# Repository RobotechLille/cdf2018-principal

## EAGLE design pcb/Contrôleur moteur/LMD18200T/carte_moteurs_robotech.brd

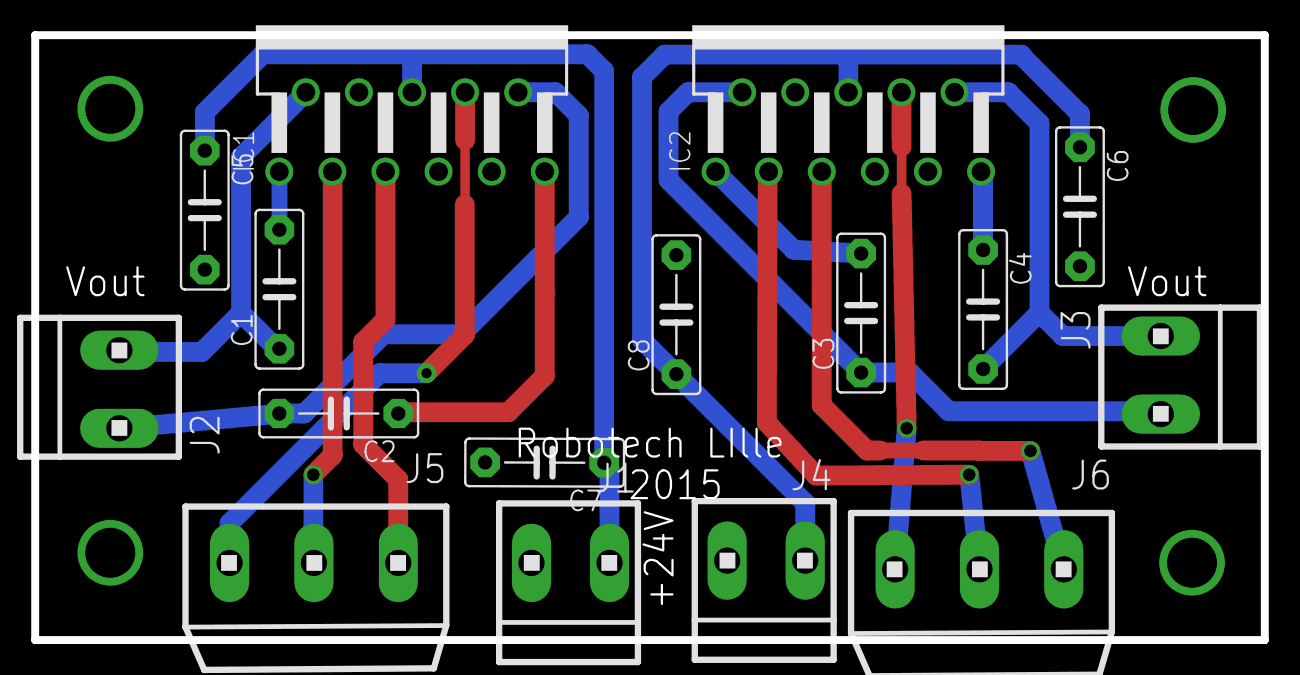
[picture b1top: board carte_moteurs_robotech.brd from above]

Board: 2 copper layers, 78.7 x 38.7 mm, 20 parts (0 on the bottom side), 16 nets.

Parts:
C1, C2, C3, C4: 10n; C7.5B3
C5, C6, C7, C8: 100n; C7.5B3
IC1, IC2: LM18200T; TO-220-11
J1, J2, J3, J4: MYJUMPER
J5, J6: 1X3MTA
U$1, U$2, U$3, U$4: DRILL3ME

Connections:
+24V: C5.1, C7.1, IC1.6, J1.2
DROITE_COURANT: IC2.8, J6.1
DROITE_PWM: IC2.5, J6.3
DROITE_S1: C3.1, IC2.2, J3.1
DROITE_S2: C4.2, IC2.10, J3.2
DROITE_SENS: IC2.3, J6.2
GAUCHE_COURANT: IC1.8, J5.1
GAUCHE_PWM: IC1.5, J5.3
GAUCHE_S1: C1.1, IC1.2, J2.1
GAUCHE_S2: C2.2, IC1.10, J2.2
GND: C5.2, C6.2, C7.2, C8.2, IC1.4, IC1.7, IC2.4, IC2.7, J1.1, J4.1, U$1.P$1, U$2.P$1, U$3.P$1, U$4.P$1
unnamed: C1.2, IC1.1
unnamed: C2.1, IC1.11
unnamed: C3.2, IC2.1
unnamed: C4.1, IC2.11
V_BAT2: C6.1, C8.1, IC2.6, J4.2

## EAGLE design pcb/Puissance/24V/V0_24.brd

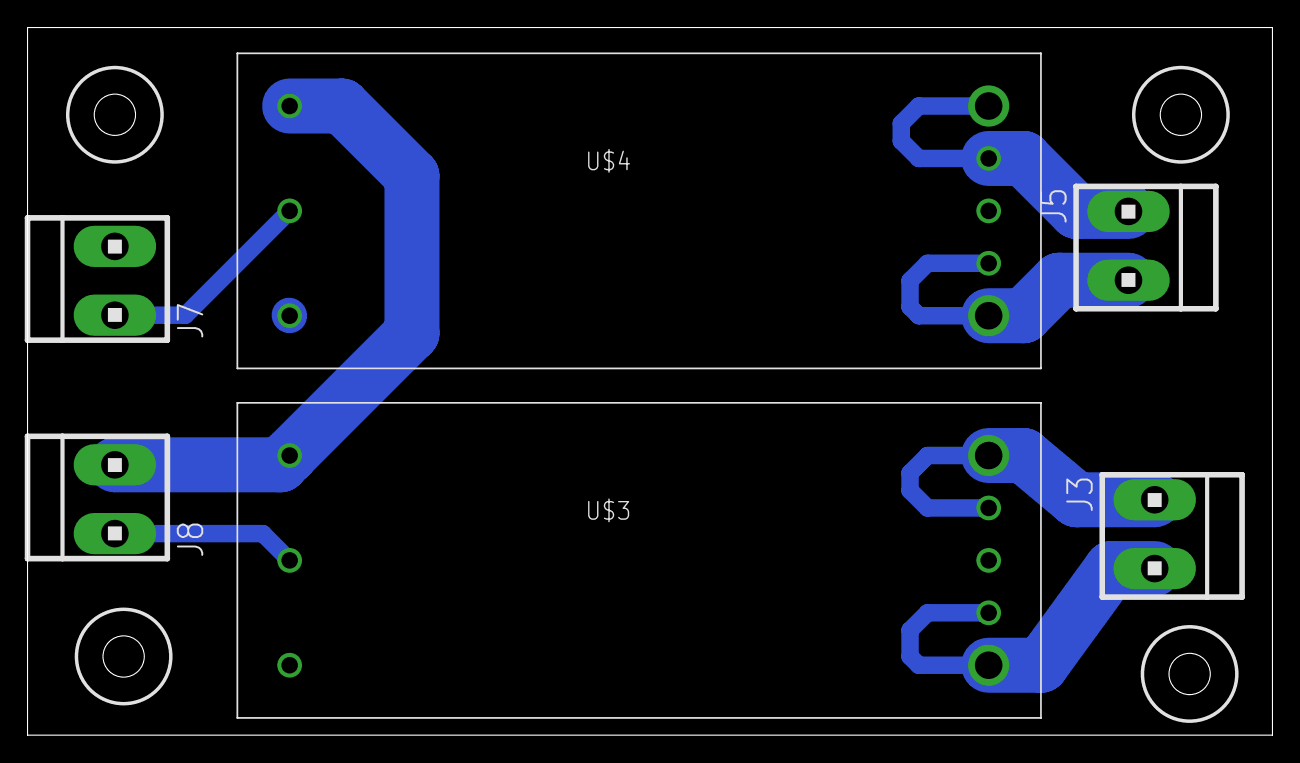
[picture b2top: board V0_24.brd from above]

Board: 2 copper layers, 90.5 x 51.4 mm, 10 parts (0 on the bottom side), 8 nets.

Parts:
J3, J5, J7, J8: MYJUMPER
U$1, U$2, U$5, U$6: DRIL-3
U$3, U$4: DC/DC_CONV_24V; UWE

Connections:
GND: J7.1, U$3.+VIN, U$4.+VIN
unnamed: J5.1, U$4.+SENSE, U$4.+VOUT
unnamed: J5.2, U$4.-SENSE, U$4.-VOUT
unnamed: J3.1, U$3.+SENSE, U$3.+VOUT
unnamed: J3.2, U$3.-SENSE, U$3.-VOUT
unnamed: J8.2, U$3.ON/OFF-CONTROL
S$2: J7.2, U$4.ON/OFF-CONTROL
S$3: J8.1, U$3.-VIN, U$4.-VIN

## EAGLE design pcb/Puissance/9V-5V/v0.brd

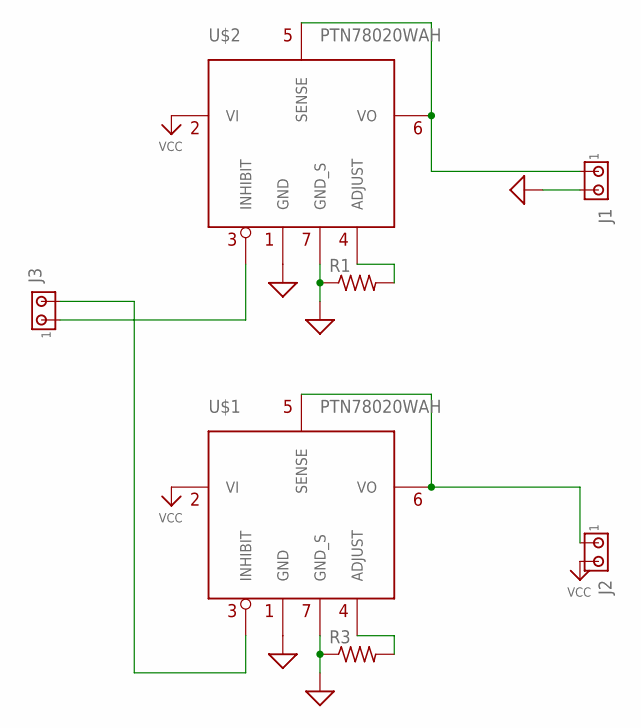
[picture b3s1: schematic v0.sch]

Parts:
J1, J2, J3: MTA02-156; MYJUMPER
R1, R3: FLIPFLOP-RES; 0805-THM
U$1, U$2: PTN78020WAH

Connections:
GND: J1.2, R1.1, R3.1, U$1.1 (GND), U$1.7 (GND_S), U$2.1 (GND), U$2.7 (GND_S)
unnamed: R1.2, U$2.4 (ADJUST)
unnamed: J2.1, U$1.5 (SENSE), U$1.6 (VO)
unnamed: J3.1, U$2.3 (INHIBIT)
unnamed: J1.1, U$2.5 (SENSE), U$2.6 (VO)
unnamed: R3.2, U$1.4 (ADJUST)
unnamed: J3.2, U$1.3 (INHIBIT)
VCC: J2.2, U$1.2 (VI), U$2.2 (VI)

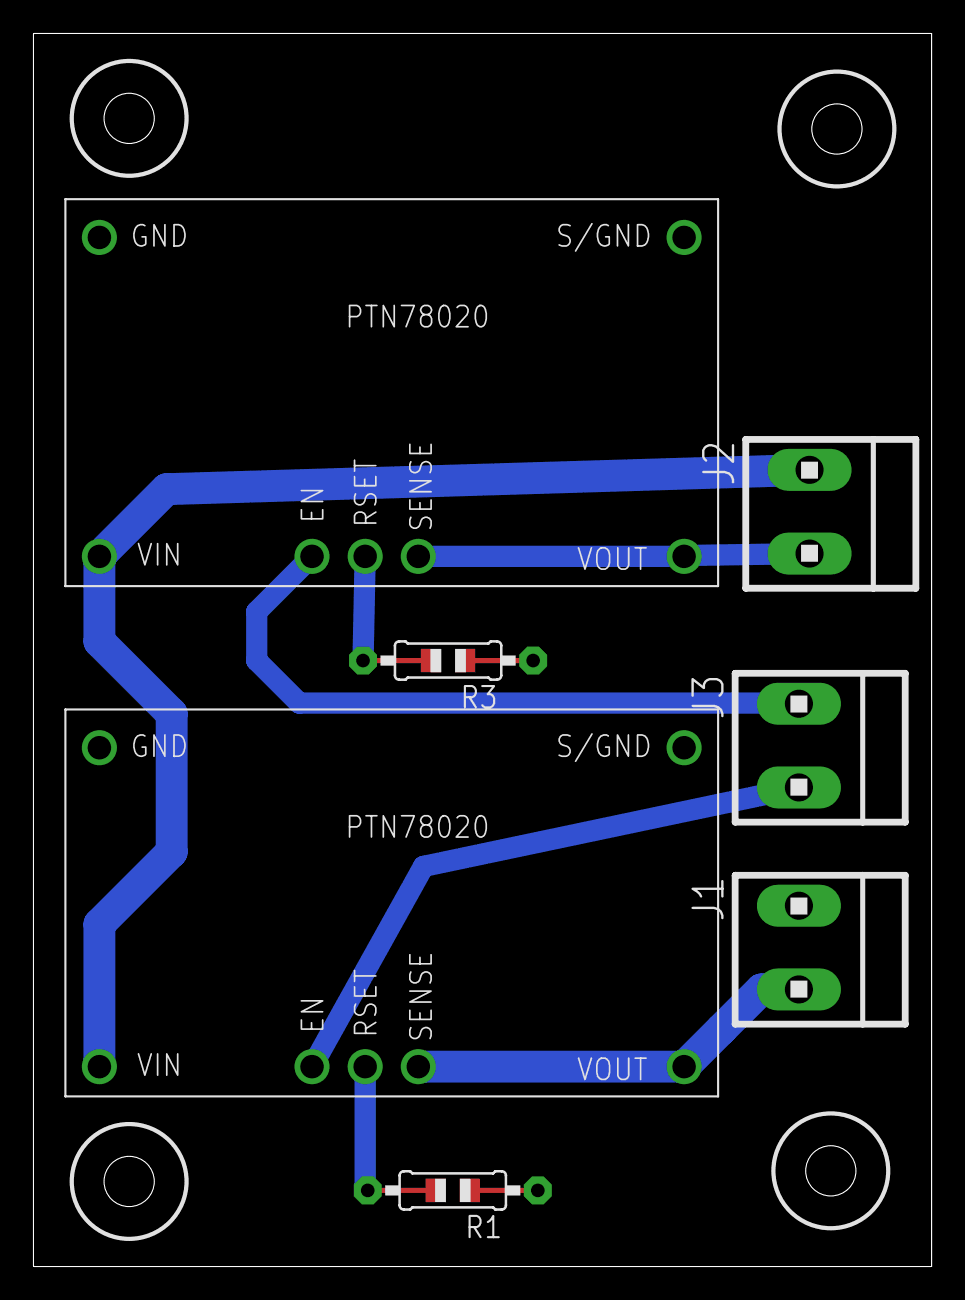
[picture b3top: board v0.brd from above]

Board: 2 copper layers, 53.6 x 73.7 mm, 11 parts (0 on the bottom side), 8 nets.

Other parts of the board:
U$3, U$4, U$5, U$6: DRIL-3

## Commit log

2018-02-07 Commit initial
2018-02-12 Communication A↔C : Base coté Arduino
2018-02-12 Communication A↔C : Base côté Chef
2018-02-14 A↔C: Développement côté Arduino
2018-02-14 Outils de debug
2018-02-16 Arduino↔Chef: Ajout côté chef & corrections
2018-02-16 Rattrapage de session abandonnée Arduino
2018-02-16 Différentiation Stop / Brake
2018-02-21 Communication du FPGA : Ajout des bases
2018-02-25 FPGA: Ajout de simulations
2018-02-25 FPGA : Amélioration code 7-segments
2018-02-25 FPGA : Communication sur plusieurs octets
2018-02-26 FPGA : Pile/cache d'envoi
2018-02-26 FPGA : Envoi de valeurs des capteurs
2018-02-27 FPGA : Gestion des encodeurs
2018-02-27 FPGA : HCSR04 et améliorations
2018-02-27 FPGA : Trigger
2018-02-28 FPGA : Filtre
2018-02-28 FPGA : Pipelinage du module de communication
2018-03-02 FPGA : Nettoyage des modules de debug
2018-03-02 FPGA : Suppression délai inutile encodeurs
2018-03-26 Travail inachevé avec Arduino
2018-03-26 Définition contrôleur moteur
2018-04-04 Récupération de la position
2018-04-29 Revamped debug interface
2018-04-29 Remote connection via PPPoE
2018-04-29 Added I2C (SRF05 & LCD)
2018-04-30 Better IHM
2018-05-01 Motor controller via FPGA
2018-05-01 Gestion des signaux
2018-05-01 Debug filename changed
2018-05-01 Diagnostics
2018-05-01 115200 baud
2018-05-02 Lowered PWM frequency
2018-05-02 Misc
2018-05-02 Misc 2
2018-05-04 Dongle Wi-Fi AR5523
    Se déconnecte tout le temps, à tester avec buildroot 2018.2
2018-05-04 ↑Buildroot
    Le dongle Wi-Fi TP-Link refonctionne en conséquence
2018-05-05 WIP IMU
2018-05-05 Fix codeuses
2018-05-06 Refined motors
2018-05-06 Bon sens des moteurs
2018-05-06 Added simulation
2018-05-06 Movement
2018-05-07 Actionneurs
    Partie Robotech hors-projet
2018-05-08 Plus d'actionneurs
2018-05-08 Hard reset LCD
2018-05-08 Peut ignorer si l'Arduino n'est pas connecté
2018-05-08 Attente fin de consigne
2018-05-08 Broche de référence pour PWM
2018-05-08 MàJ simulation
2018-05-09 Sécurité
2018-05-09 Parcours total
2018-05-09 Rate limiter
2018-05-09 Update code Arduino
    Robotech again
2018-05-09 WIP Contrôle
2018-05-10 Tolérance au loupage de message du FPGA
2018-05-10 Réécriture du système de consigne
2018-05-10 Ajout de deux capteurs à ultrasons
2018-05-11 Serial → I2C
2018-05-12 Gestion correcte de l'asservissement
2018-05-16 Meilleur asservissement
2018-05-16 Essai de calibrage en position
2018-05-16 Ajout des PCB
